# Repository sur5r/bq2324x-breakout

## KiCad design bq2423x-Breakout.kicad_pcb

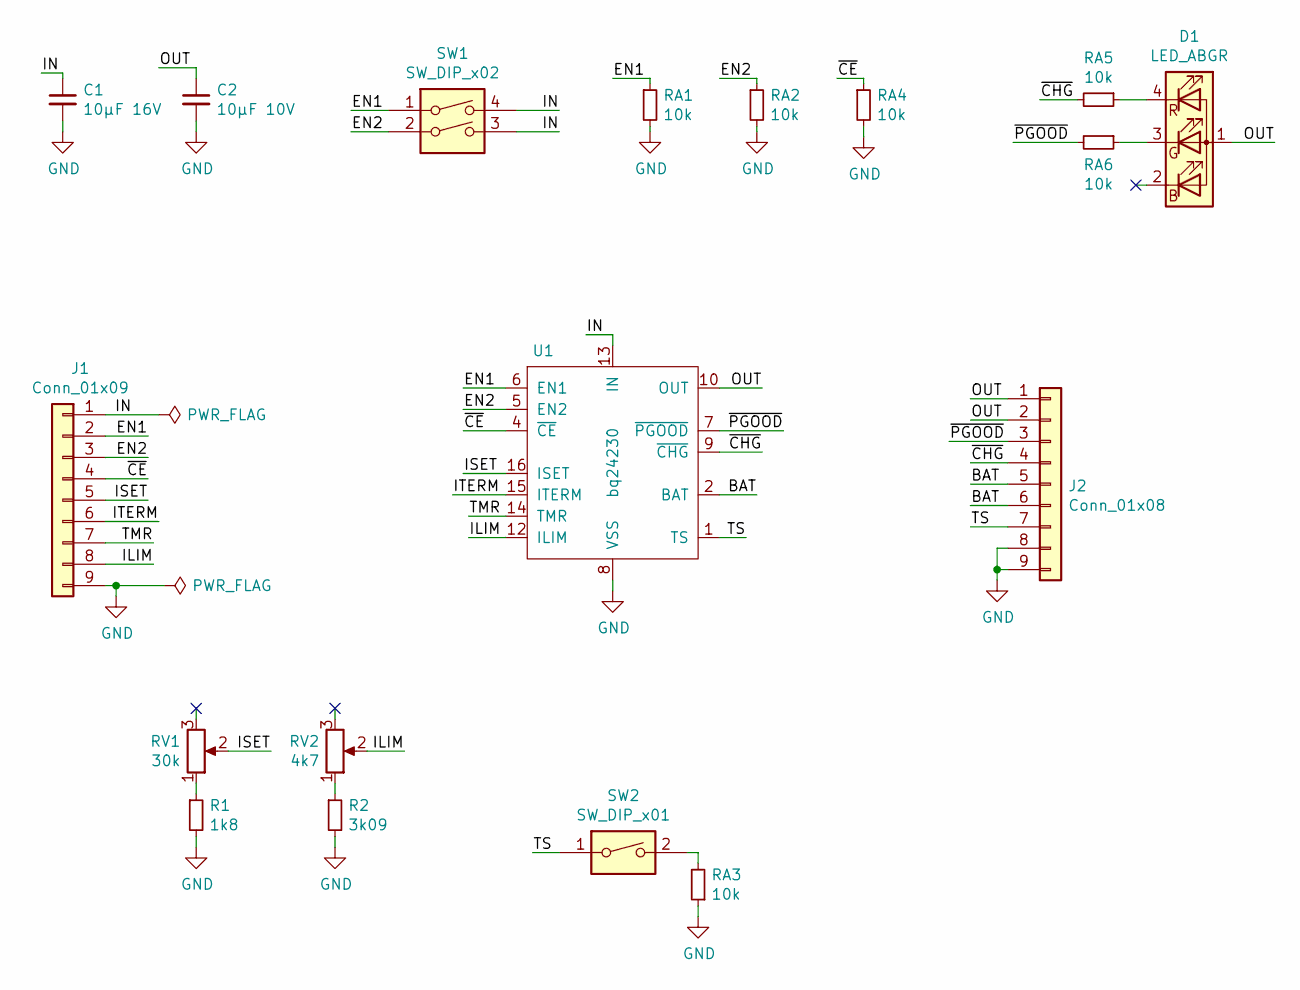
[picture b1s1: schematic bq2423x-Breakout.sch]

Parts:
C1: 10µF 16V; C_0603_1608Metric; MPN EMK107BBJ106MA-T
C2: 10µF 10V; C_0603_1608Metric; MPN 0603ZD106KAT2A
D1: LED_ABGR; LED_Cree-PLCC4_2x2mm_CW; MPN CLMVC-FKA-CL1D1L71BB7C3C3
J1: Conn_01x09; PinHeader_1x09_P2.54mm_Vertical
J2: Conn_01x08; PinHeader_1x09_P2.54mm_Vertical
R1: 1k8; R_0603_1608Metric; MPN RC0603FR-071K8L
R2: 3k09; R_0603_1608Metric; MPN RC0603FR-073K09L
RA1, RA2, RA3, RA4, RA5, RA6: 10k; R_0603_1608Metric; MPN RC0603JR-071KL
RV1: 30k; Potentiometer_Bourns_TC33X_Vertical; MPN TC33X-2-303ECT-ND
RV2: 4k7; Potentiometer_Bourns_3314J_Vertical; MPN 3314J-1-472E
SW1: SW_DIP_x02; SW_DIP_SPSTx02_Slide_Copal_CHS-02A_W5.08mm_P1.27mm_JPin; MPN CHS-02TA
SW2: SW_DIP_x01; SW_DIP_SPSTx01_Slide_Copal_CHS-01A_W5.08mm_P1.27mm_JPin; MPN CHS-01TA
U1: bq24230; QFN-16-1EP_3x3mm_P0.5mm_EP1.7x1.7mm_ThermalVias; MPN BQ24230RGTR

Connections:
/BAT: J2.5, J2.6, U1.2 (BAT), U1.3 (BAT)
/EN1: J1.2, RA1.1, SW1.1, U1.6 (EN1)
/EN2: J1.3, RA2.1, SW1.2, U1.5 (EN2)
/ILIM: J1.8, RV2.2, U1.12 (ILIM)
/IN: C1.1, J1.1, SW1.3, SW1.4, U1.13 (IN)
/ISET: J1.5, RV1.2, U1.16 (ISET)
/ITERM: J1.6, U1.15 (ITERM)
/OUT: C2.1, D1.1 (A), J2.1, J2.2, U1.10 (OUT), U1.11 (OUT)
/TMR: J1.7, U1.14 (TMR)
/TS: J2.7, SW2.1, U1.1 (TS)
/~CE: J1.4, RA4.1, U1.4 (~CE)
/~CHG: J2.4, RA5.2, U1.9 (~CHG)
/~PGOOD: J2.3, RA6.2, U1.7 (~PGOOD)
GND: C1.2, C2.2, J1.9, J2.8, J2.9, R1.2, R2.2, RA1.2, RA2.2, RA3.1, RA4.2, U1.8 (VSS), U1.17
unnamed: D1.3 (GK), RA6.1
unnamed: D1.4 (RK), RA5.1
unnamed: R1.1, RV1.1
unnamed: R2.1, RV2.1
unnamed: RA3.2, SW2.2

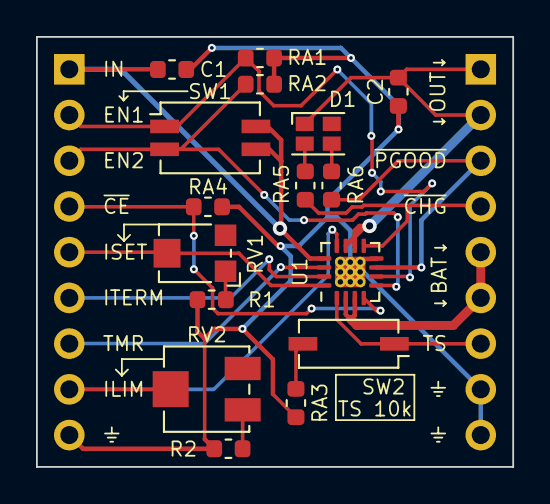
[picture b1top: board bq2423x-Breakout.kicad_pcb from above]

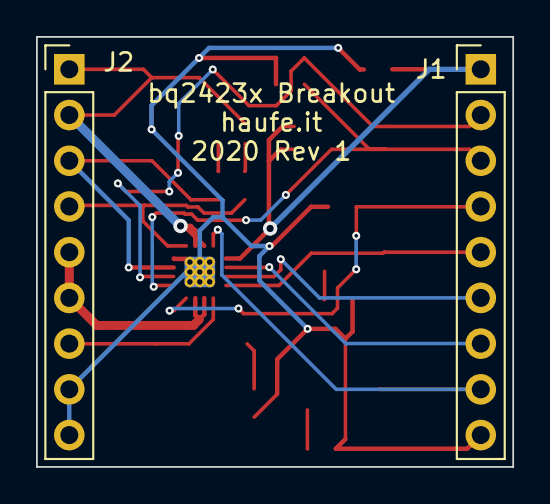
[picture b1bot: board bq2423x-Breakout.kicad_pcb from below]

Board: 2 copper layers, 26.5 x 23.9 mm, 18 parts (2 on the bottom side), 19 nets.

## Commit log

2020-07-24 Preliminary layout
2020-07-27 Improve Silkscreen
2020-07-27 Fix MPN/etc. for RA*
